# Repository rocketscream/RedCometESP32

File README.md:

# Red Comet ESP32

An ultra low power ESP32 board. The board is able to run from variety type of battery below and above it's 3.3V operating voltage. This allow batteries such as 3xNiMH or 4xNiMH, Li-Ion/Pol, 3 or 4 alkaline and LiFePO4 to be used. Board sleep at 13.0 uA with charger off.

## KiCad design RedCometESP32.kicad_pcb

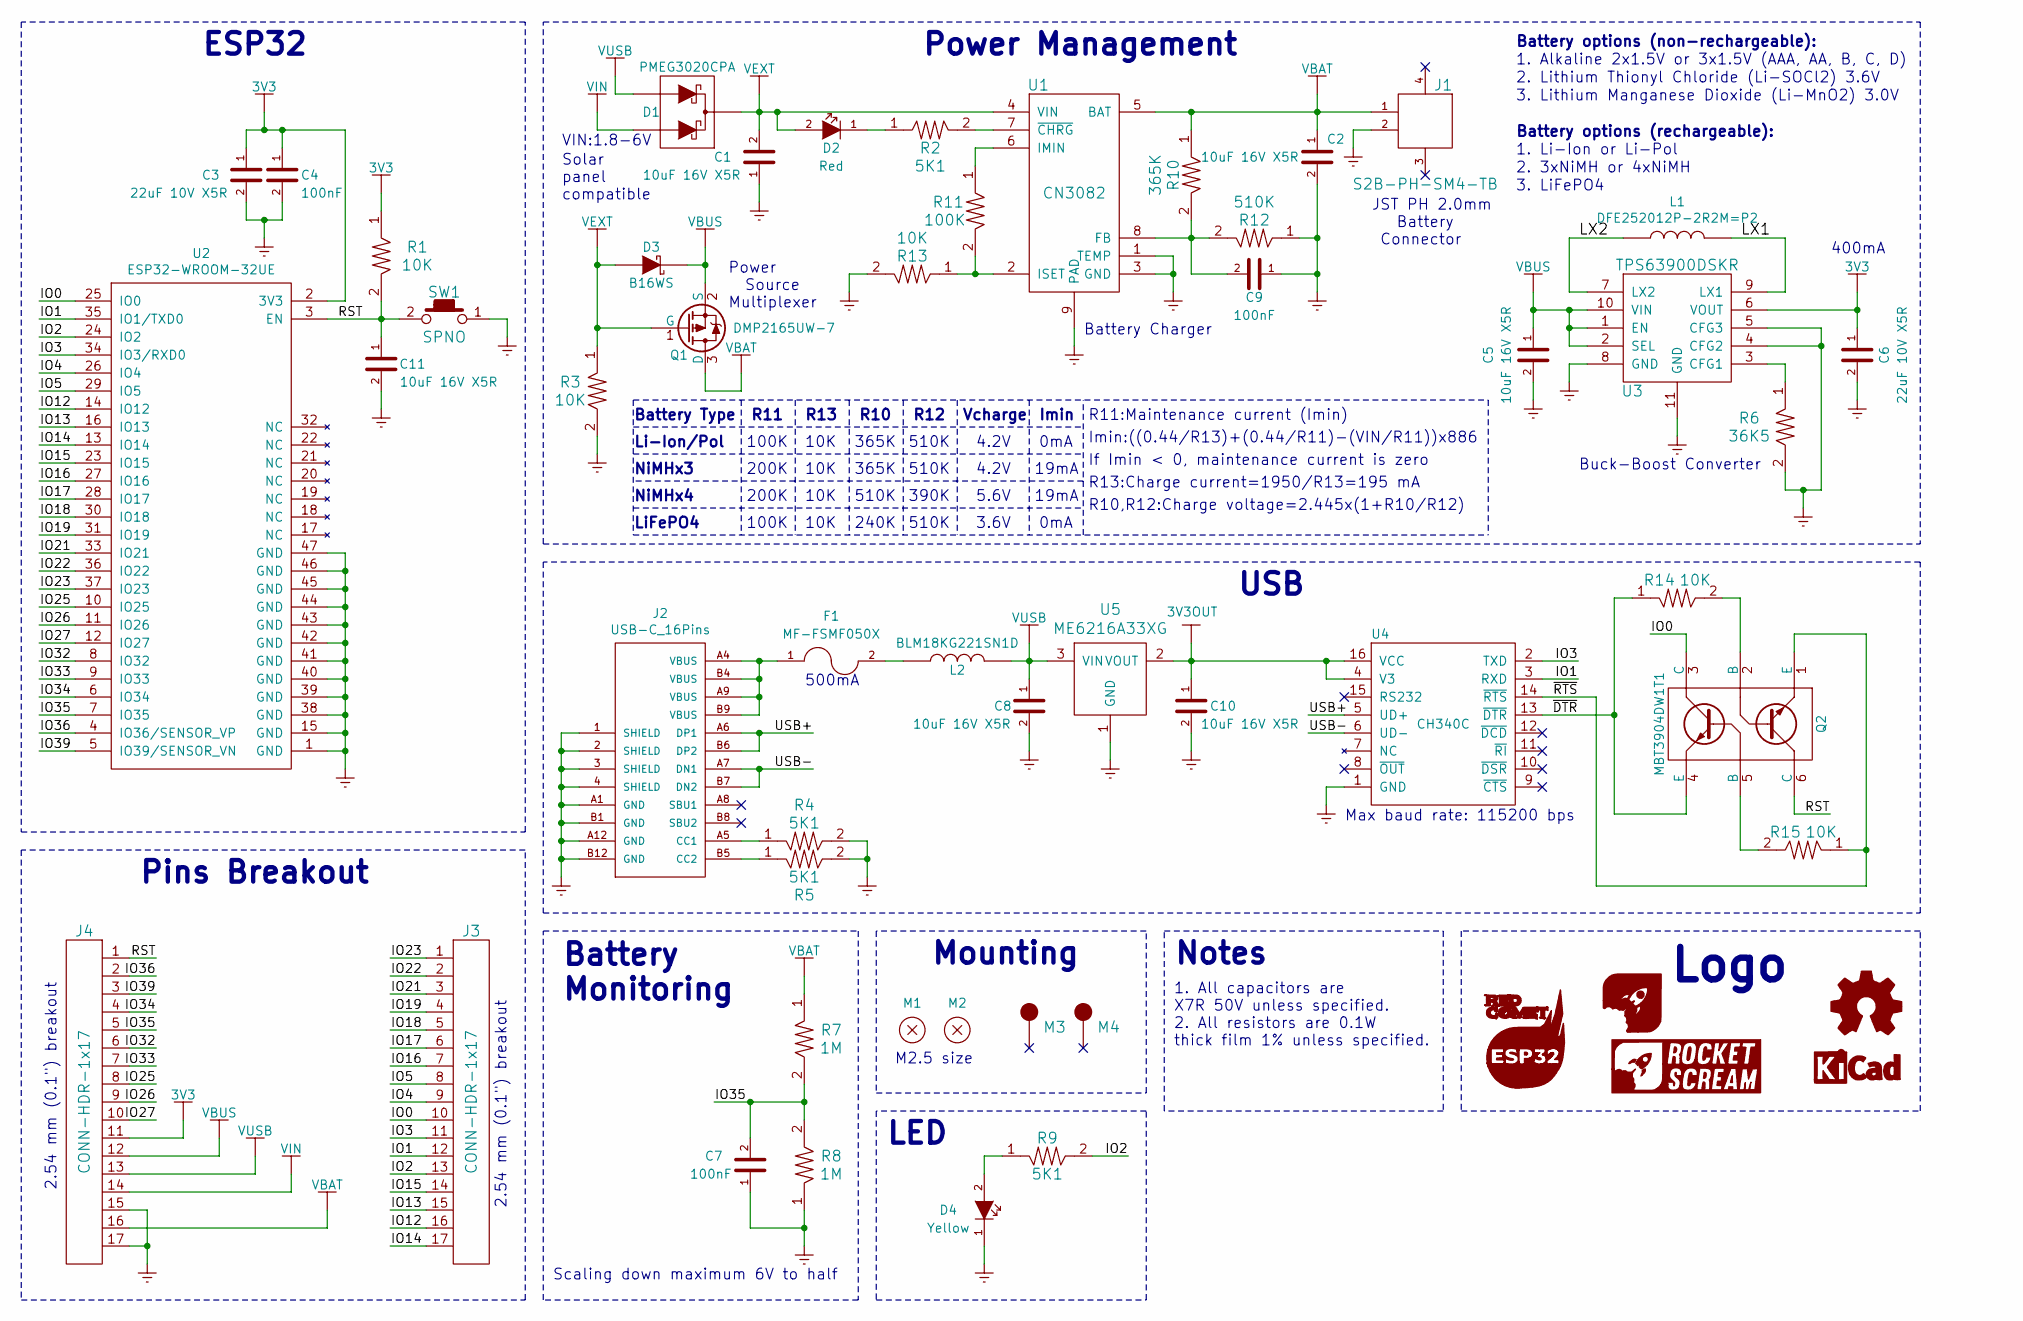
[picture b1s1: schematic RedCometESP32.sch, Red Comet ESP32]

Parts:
C1, C2, C5, C8, C10, C11: 10uF 16V X5R; C_0603
C3, C6: 22uF 10V X5R; C_0603
C4, C7, C9: 100nF; C_0603
D1: PMEG3020CPA; SOT-1016
D2: Red; LED_0603
D3: B16WS; SOD-323
D4: Yellow; LED_0603
F1: MF-FSMF050X; MF-FSMF
J1: S2B-PH-SM4-TB
J2: USB-C_16Pins; USB-TYPE-C-16PIN-SMD
J3, J4: CONN-HDR-1x17; HDR_1x17_Pitch2.54mm_WithoutSilk_SmallerPads
L1: DFE252012P-2R2M=P2; DFE2520
L2: BLM18KG221SN1D; I_0603
LOGO1: LOGO-OSHW; LOGO-OSHW_XXSmall
LOGO2: LOGO-KICAD; LOGO-KICAD_XSmall
LOGO3: LOGO-ROCKET-SCREAM-HORIZONTAL; LOGO-ROCKET-SCREAM_Horizontal_XXSmall
LOGO4: LOGO-ROCKET-SCREAM-WITHOUT-TEXT; LOGO-ROCKET-SCREAM_Without_Text_XXXXSmall
LOGO5: LOGO-RED-COMET-ESP32; LOGO-RED-COMET-ESP32_Large
M1, M2: MOUNT_HOLE; HOLE_NPTH_2.2MM
M3, M4: FIDUCIAL; FIDUCIAL-0.5MM_SQUARE
Q1: DMP2165UW-7; SOT-323
Q2: MBT3904DW1T1; SOT-363_ON_Semi
R1, R3, R13, R14, R15: 10K; R_0603
R2, R4, R5, R9: 5K1; R_0603
R6: 36K5; R_0603
R7, R8: 1M; R_0603
R10: 365K; R_0603
R11: 100K; R_0603
R12: 510K; R_0603
SW1: SPNO; TS-107A
U1: CN3082; SOIC-8-N_8S1_ThermalPad
U2: ESP32-WROOM-32UE; ESP32-WROOM-32UE_ShorterPads
U3: TPS63900DSKR; WSON-10
U4: CH340C; SOP-16_150mil
U5: ME6216A33XG; SOT-23

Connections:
3V3: C3.1, C4.1, C6.1, J4.11, R1.1, U2.2 (3V3), U3.6 (VOUT)
3V3OUT: C10.1, U4.4 (V3), U4.16 (VCC), U5.2 (VOUT)
/IO0: J3.10, Q2.3 (C), U2.25 (IO0)
/IO1: J3.12, U2.35 (IO1/TXD0), U4.3 (RXD)
/IO2: J3.13, R9.2, U2.24 (IO2)
/IO3: J3.11, U2.34 (IO3/RXD0), U4.2 (TXD)
/IO4: J3.9, U2.26 (IO4)
/IO5: J3.8, U2.29 (IO5)
/IO12: J3.16, U2.14 (IO12)
/IO13: J3.15, U2.16 (IO13)
/IO14: J3.17, U2.13 (IO14)
/IO15: J3.14, U2.23 (IO15)
/IO16: J3.7, U2.27 (IO16)
/IO17: J3.6, U2.28 (IO17)
/IO18: J3.5, U2.30 (IO18)
/IO19: J3.4, U2.31 (IO19)
/IO21: J3.3, U2.33 (IO21)
/IO22: J3.2, U2.36 (IO22)
/IO23: J3.1, U2.37 (IO23)
/IO25: J4.8, U2.10 (IO25)
/IO26: J4.9, U2.11 (IO26)
/IO27: J4.10, U2.12 (IO27)
/IO32: J4.6, U2.8 (IO32)
/IO33: J4.7, U2.9 (IO33)
/IO34: J4.4, U2.6 (IO34)
/IO35: C7.2, J4.5, R7.2, R8.2, U2.7 (IO35)
/IO36: J4.2, U2.4 (IO36/SENSOR_VP)
/IO39: J4.3, U2.5 (IO39/SENSOR_VN)
/LX1: L1.2, U3.9 (LX1)
/LX2: L1.1, U3.7 (LX2)
/RST: C11.1, J4.1, Q2.6 (C), R1.2, SW1.2, U2.3 (EN)
/USB+: J2.A6 (DP1), J2.B6 (DP2), U4.5 (UD+)
/USB-: J2.A7 (DN1), J2.B7 (DN2), U4.6 (UD-)
/~DTR~: Q2.4 (E), R14.1, U4.13 (~DTR)
/~RTS~: Q2.1 (E), R15.1, U4.14 (~RTS)
GND: C1.1, C2.2, C3.2, C4.2, C5.2, C6.2, C7.1, C8.2, C9.1, C10.2, C11.2, D4.1 (K), J1.2, J2.1 (SHIELD), J2.2 (SHIELD), J2.3 (SHIELD), J2.4 (SHIELD), J2.A1 (GND), J2.A12 (GND), J2.B1 (GND), J2.B12 (GND), J4.15, J4.17, R3.2, R4.2, R5.2, R6.2, R8.1, R12.1, R13.2, SW1.1, U1.1 (TEMP), U1.3 (GND), U1.9 (PAD), U2.1 (GND), U2.15 (GND), U2.38 (GND), U2.39 (GND), U2.40 (GND), U2.41 (GND), U2.42 (GND), U2.43 (GND), U2.44 (GND), U2.45 (GND), U2.46 (GND), U2.47 (GND), U3.4 (CFG2), U3.5 (CFG3), U3.8 (GND), U3.11 (GND), U4.1 (GND), U5.1 (GND)
unnamed: C9.2, R10.2, R12.2, U1.8 (FB)
unnamed: D2.1 (K), R2.1
unnamed: D4.2 (A), R9.1
unnamed: F1.1, J2.A4 (VBUS), J2.A9 (VBUS), J2.B4 (VBUS), J2.B9 (VBUS)
unnamed: F1.2, L2.1
unnamed: J2.A5 (CC1), R4.1
unnamed: J2.B5 (CC2), R5.1
unnamed: Q2.2 (B), R14.2
unnamed: Q2.5 (B), R15.2
unnamed: R2.2, U1.7 (~CHRG~)
unnamed: R6.1, U3.3 (CFG1)
unnamed: R11.1, U1.6 (IMIN)
unnamed: R11.2, R13.1, U1.2 (ISET)
VBAT: C2.1, J1.1, J4.16, Q1.3 (D), R7.1, R10.1, U1.5 (BAT)
VBUS: C5.1, D3.1 (K), J4.12, Q1.2 (S), U3.1 (EN), U3.2 (SEL), U3.10 (VIN)
VEXT: C1.2, D1.3 (K), D2.2 (A), D3.2 (A), Q1.1 (G), R3.1, U1.4 (VIN)
VIN: D1.2 (A), J4.14
VUSB: C8.1, D1.1 (A), J4.13, L2.2, U5.3 (VIN)

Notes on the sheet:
Logo
Mounting
Pins Breakout
LED
Battery Charger
USB
ESP32
VIN:1.8-6V
Notes
1. All capacitors are X7R 50V unless specified. 2. All resistors are 0.1W thick film 1% unless specified.
M2.5 size
2.54 mm (0.1") breakout
500mA
Battery Monitoring
Scaling down maximum 6V to half
JST PH 2.0mm Battery Connector
Solar panel compatible
Power Source Multiplexer
Buck-Boost Converter
400mA
Battery options (rechargeable):
1. Li-Ion or Li-Pol
2. 3xNiMH or 4xNiMH
3. LiFePO4
Battery options (non-rechargeable):
1. Alkaline 2x1.5V or 3x1.5V (AAA, AA, B, C, D)
3. Lithium Manganese Dioxide (Li-MnO2) 3.0V
Power Management
Battery Type
Li-Ion/Pol
NiMHx3
NiMHx4
LiFePO4
R11
R13
R10
R12
100K
200K
10K

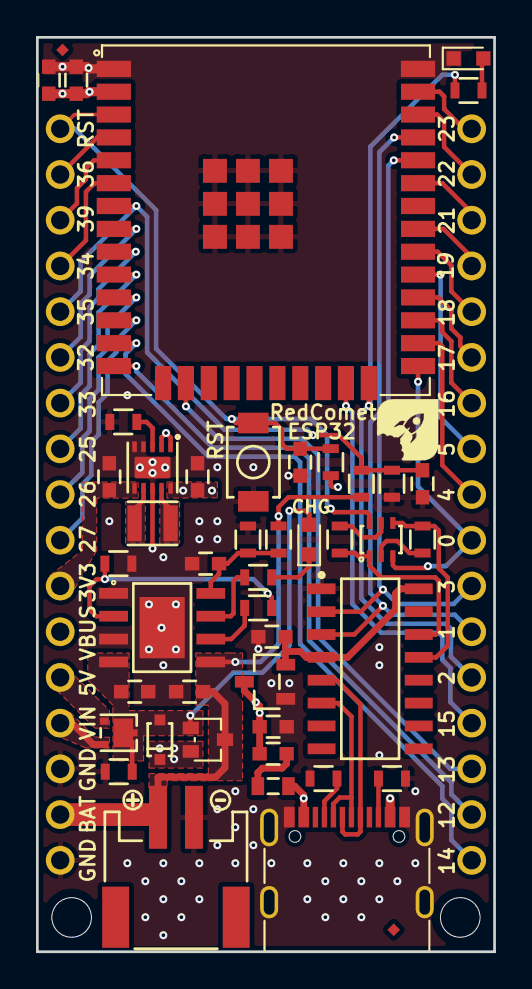
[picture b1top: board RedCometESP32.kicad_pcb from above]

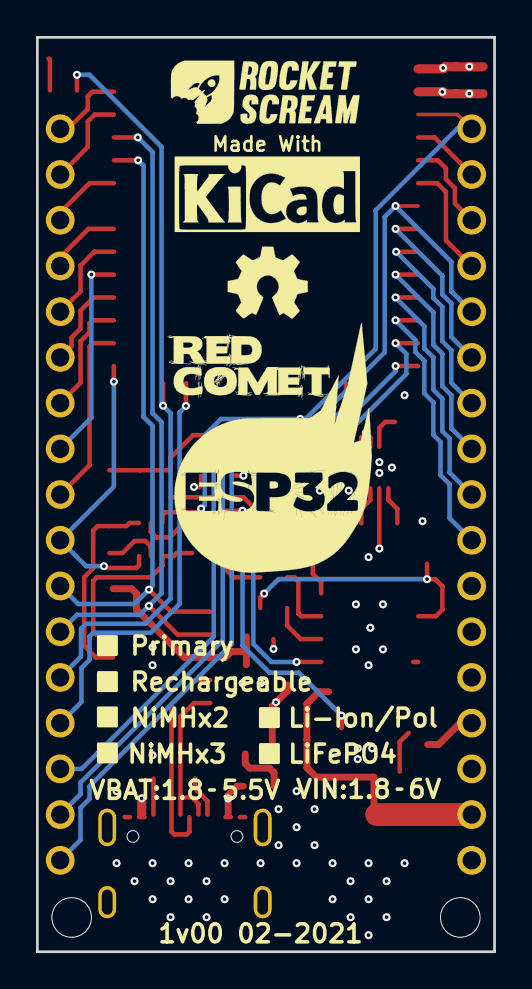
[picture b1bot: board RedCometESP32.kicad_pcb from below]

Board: 4 copper layers, 25.4 x 50.8 mm, 54 parts (6 on the bottom side), 54 nets.

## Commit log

2021-05-12 Initial public release. v1.00
